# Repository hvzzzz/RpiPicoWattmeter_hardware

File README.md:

# RpiPicoWattmeter_hardware
KiCad design files for a wattmeter built with a Raspberry Pi Pico and an INA219 power monitor.

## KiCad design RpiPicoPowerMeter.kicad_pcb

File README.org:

#+title: Rpi Pico Wattmeter Hardware

This repository contains the PCB design of the wattmeter.

General connections with Raspberry Pi 4B and data collection PC.

[[./images/watt_mod.png]]

3d view of the board
[[./images/RpiPicoPowerMeter.png]]

Physical board
[[./images/physical.jpeg]]

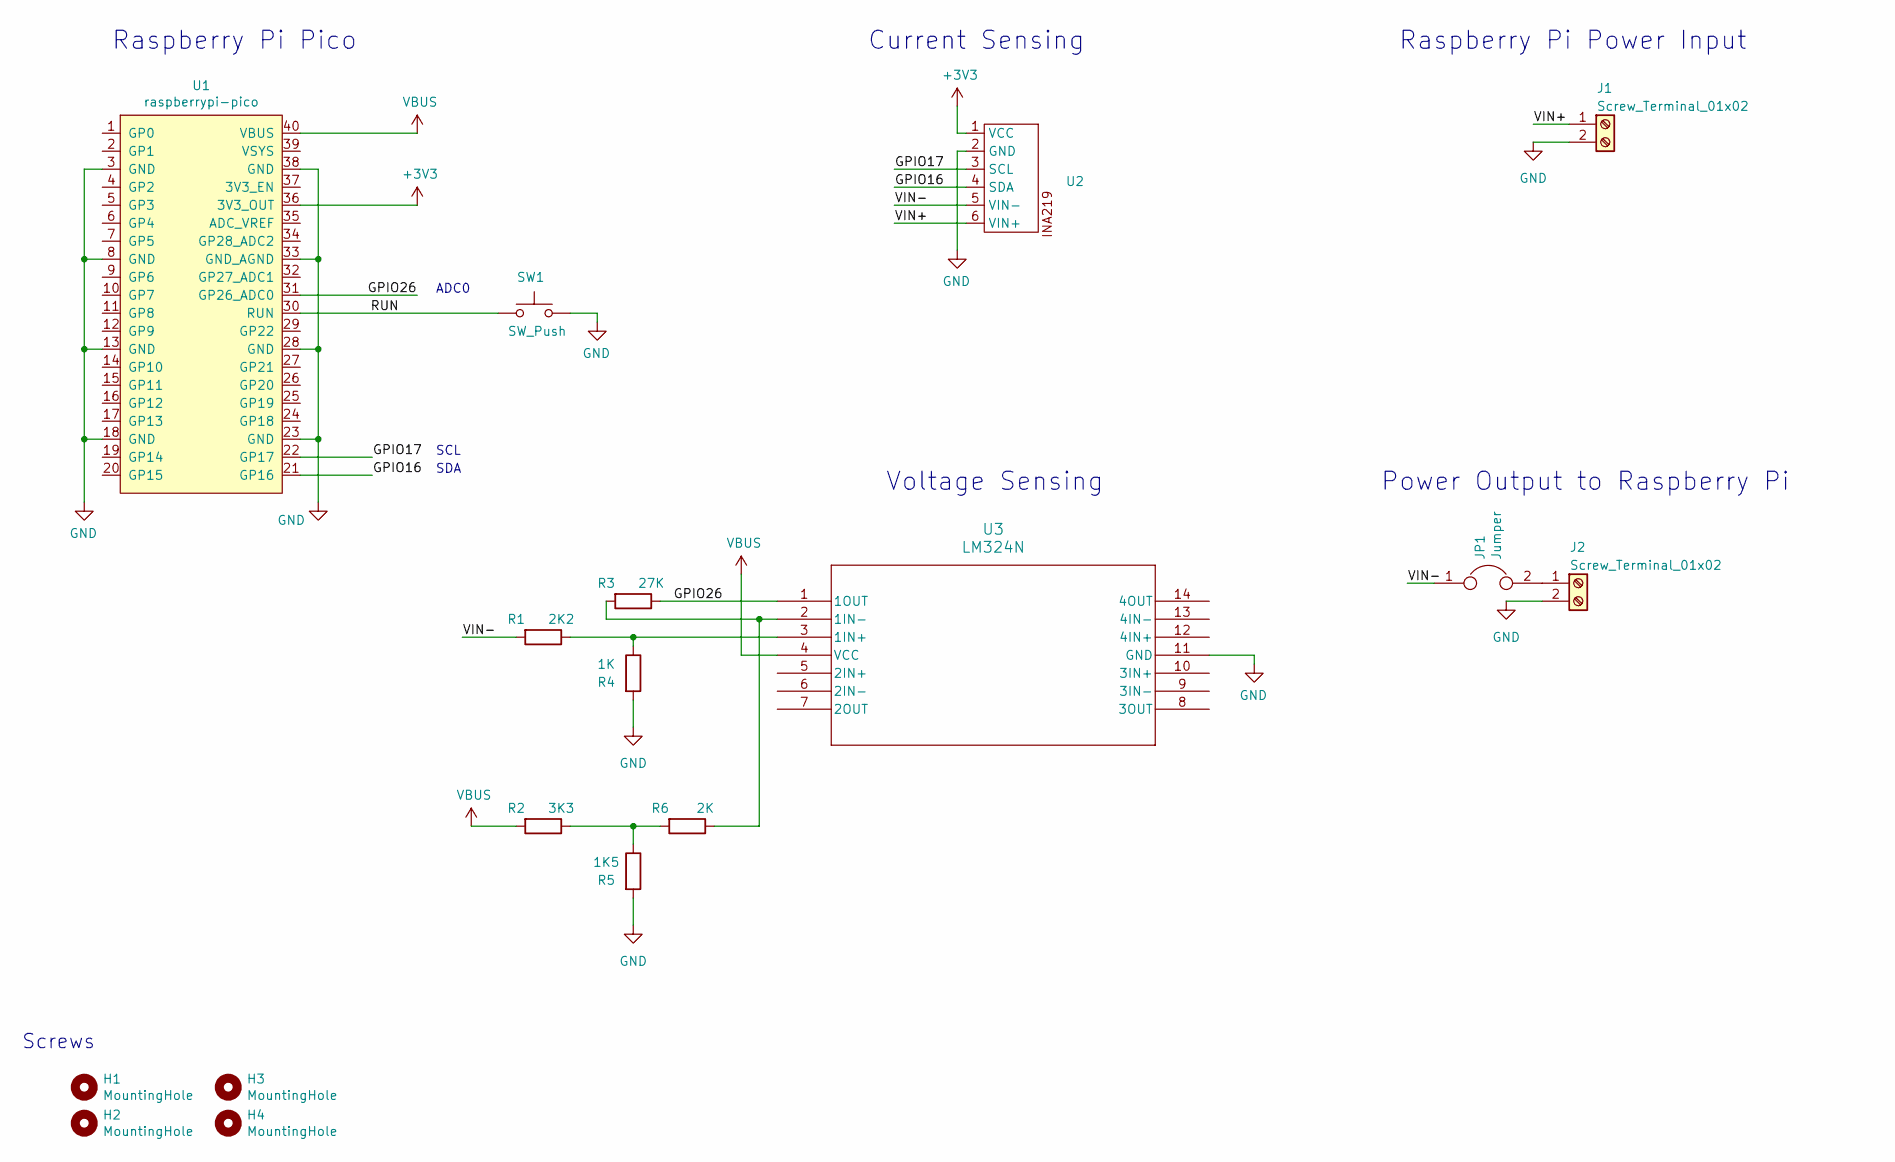
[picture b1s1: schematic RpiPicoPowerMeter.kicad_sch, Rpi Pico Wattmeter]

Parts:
H1, H2, H3, H4: MountingHole; MountingHole_2.2mm_M2
J1, J2: Screw_Terminal_01x02; TerminalBlock_bornier-2_P5.08mm
JP1: Jumper; PinHeader_1x02_P2.54mm_Vertical
R1: 2K2; R_Axial_DIN0207_L6.3mm_D2.5mm_P7.62mm_Horizontal
R2: 3K3; R_Axial_DIN0207_L6.3mm_D2.5mm_P7.62mm_Horizontal
R3: 27K; R_Axial_DIN0207_L6.3mm_D2.5mm_P7.62mm_Horizontal
R4: 1K; R_Axial_DIN0207_L6.3mm_D2.5mm_P7.62mm_Horizontal
R5: 1K5; R_Axial_DIN0207_L6.3mm_D2.5mm_P7.62mm_Horizontal
R6: 2K; R_Axial_DIN0207_L6.3mm_D2.5mm_P7.62mm_Horizontal
SW1: SW_Push; SW_PUSH_1P1T_6x3.5mm_H5.0_APEM_MJTP1250
U1: raspberrypi-pico; raspberrypi-pico-module
U2: LM219; ina219
U3: LM324N; N14

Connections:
+3V3: U1.36 (3V3_OUT), U2.1 (VCC)
/GPIO16: U1.21 (GP16), U2.4 (SDA)
/GPIO17: U1.22 (GP17), U2.3 (SCL)
/GPIO26: R3.1, U1.31 (GP26_ADC0), U3.1 (1OUT)
/RUN: SW1.1, U1.30 (RUN)
/VIN+: J1.1, U2.6 (VIN+)
/VIN-: JP1.1, R1.2, U2.5 (VIN-)
GND: J1.2, J2.2, R4.2, R5.2, SW1.2, U1.3 (GND), U1.8 (GND), U1.13 (GND), U1.18 (GND), U1.23 (GND), U1.28 (GND), U1.33 (GND_AGND), U1.38 (GND), U2.2 (GND), U3.11 (GND)
unnamed: J2.1, JP1.2
unnamed: R2.1, R5.1, R6.2
unnamed: R1.1, R4.1, U3.3 (1IN+)
unnamed: R3.2, R6.1, U3.2 (1IN-)
VBUS: R2.2, U1.40 (VBUS), U3.4 (VCC)

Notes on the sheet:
Raspberry Pi Pico
Raspberry Pi Power Input
Voltage Sensing
Power Output to Raspberry Pi
SDA
Current Sensing
ADC0
Screws
SCL

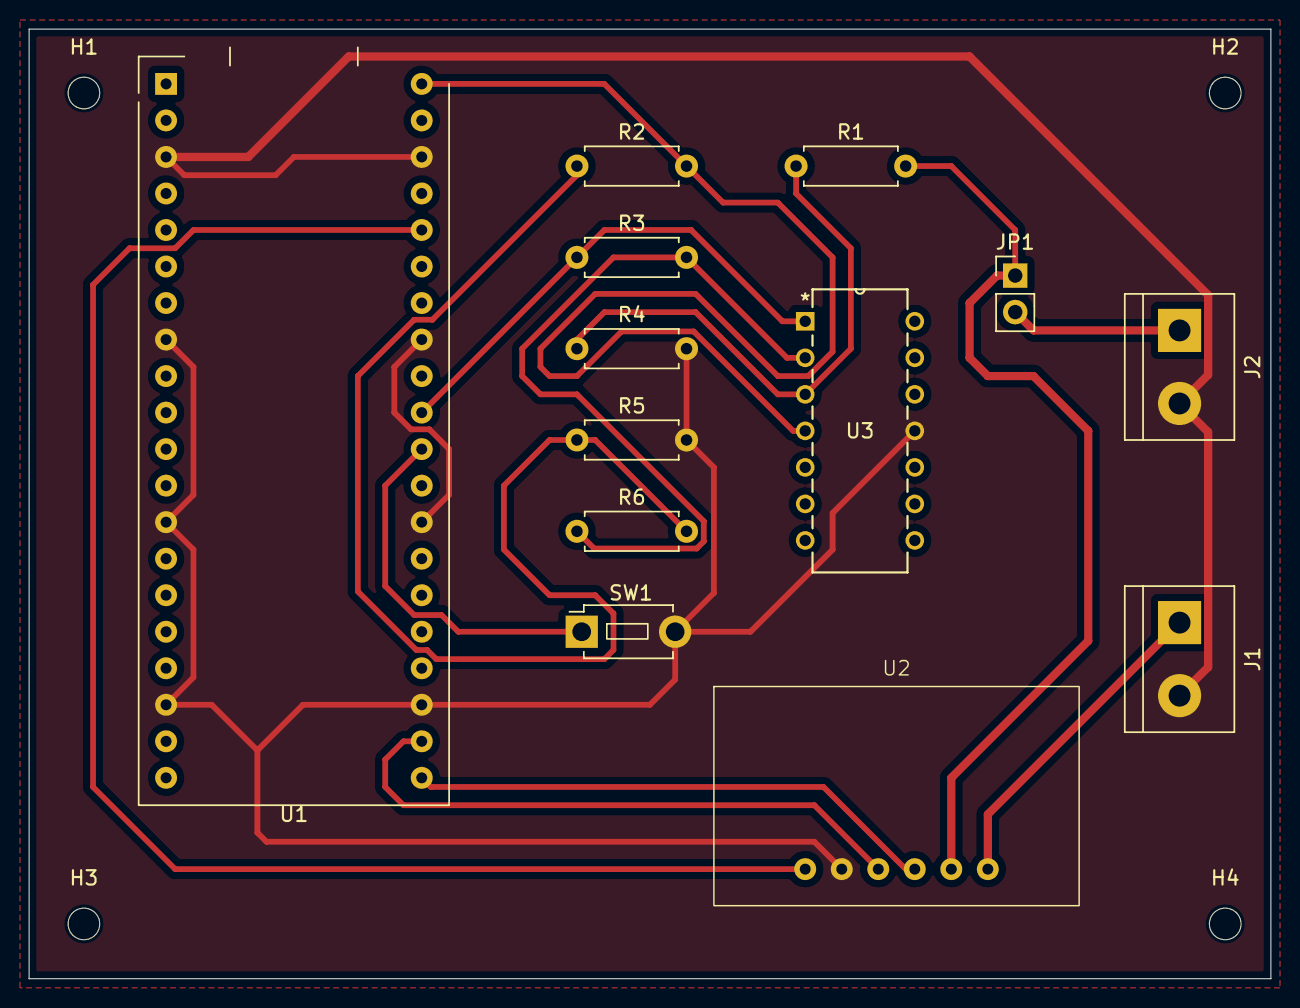
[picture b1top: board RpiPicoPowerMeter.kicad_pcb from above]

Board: 2 copper layers, 86.4 x 66.0 mm, 17 parts (0 on the bottom side), 13 nets.

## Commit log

2024-10-30 pcb files for RpiPicoWattmeter

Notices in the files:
RpiPicoPowerMeter.kicad_pcb:
creativecommons.org/licenses/by/4.0
License: CC BY 4.0
